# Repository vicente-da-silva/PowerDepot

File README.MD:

# Power Depot FJ Overland Build
## V1.0
The project started out with the goal of building a simple drawer system for my FJ. That simple goal turned into this Power Depot project! I may decide to split this project into 2 in the future as the Power Depot electronics evolve but for now the electrical and drawer system is presented as a single project.
Check out the detailed assembly document PowerDepotV1.pdf
It should be possible to easily create designs for other vehicles using the parts designed in this project.

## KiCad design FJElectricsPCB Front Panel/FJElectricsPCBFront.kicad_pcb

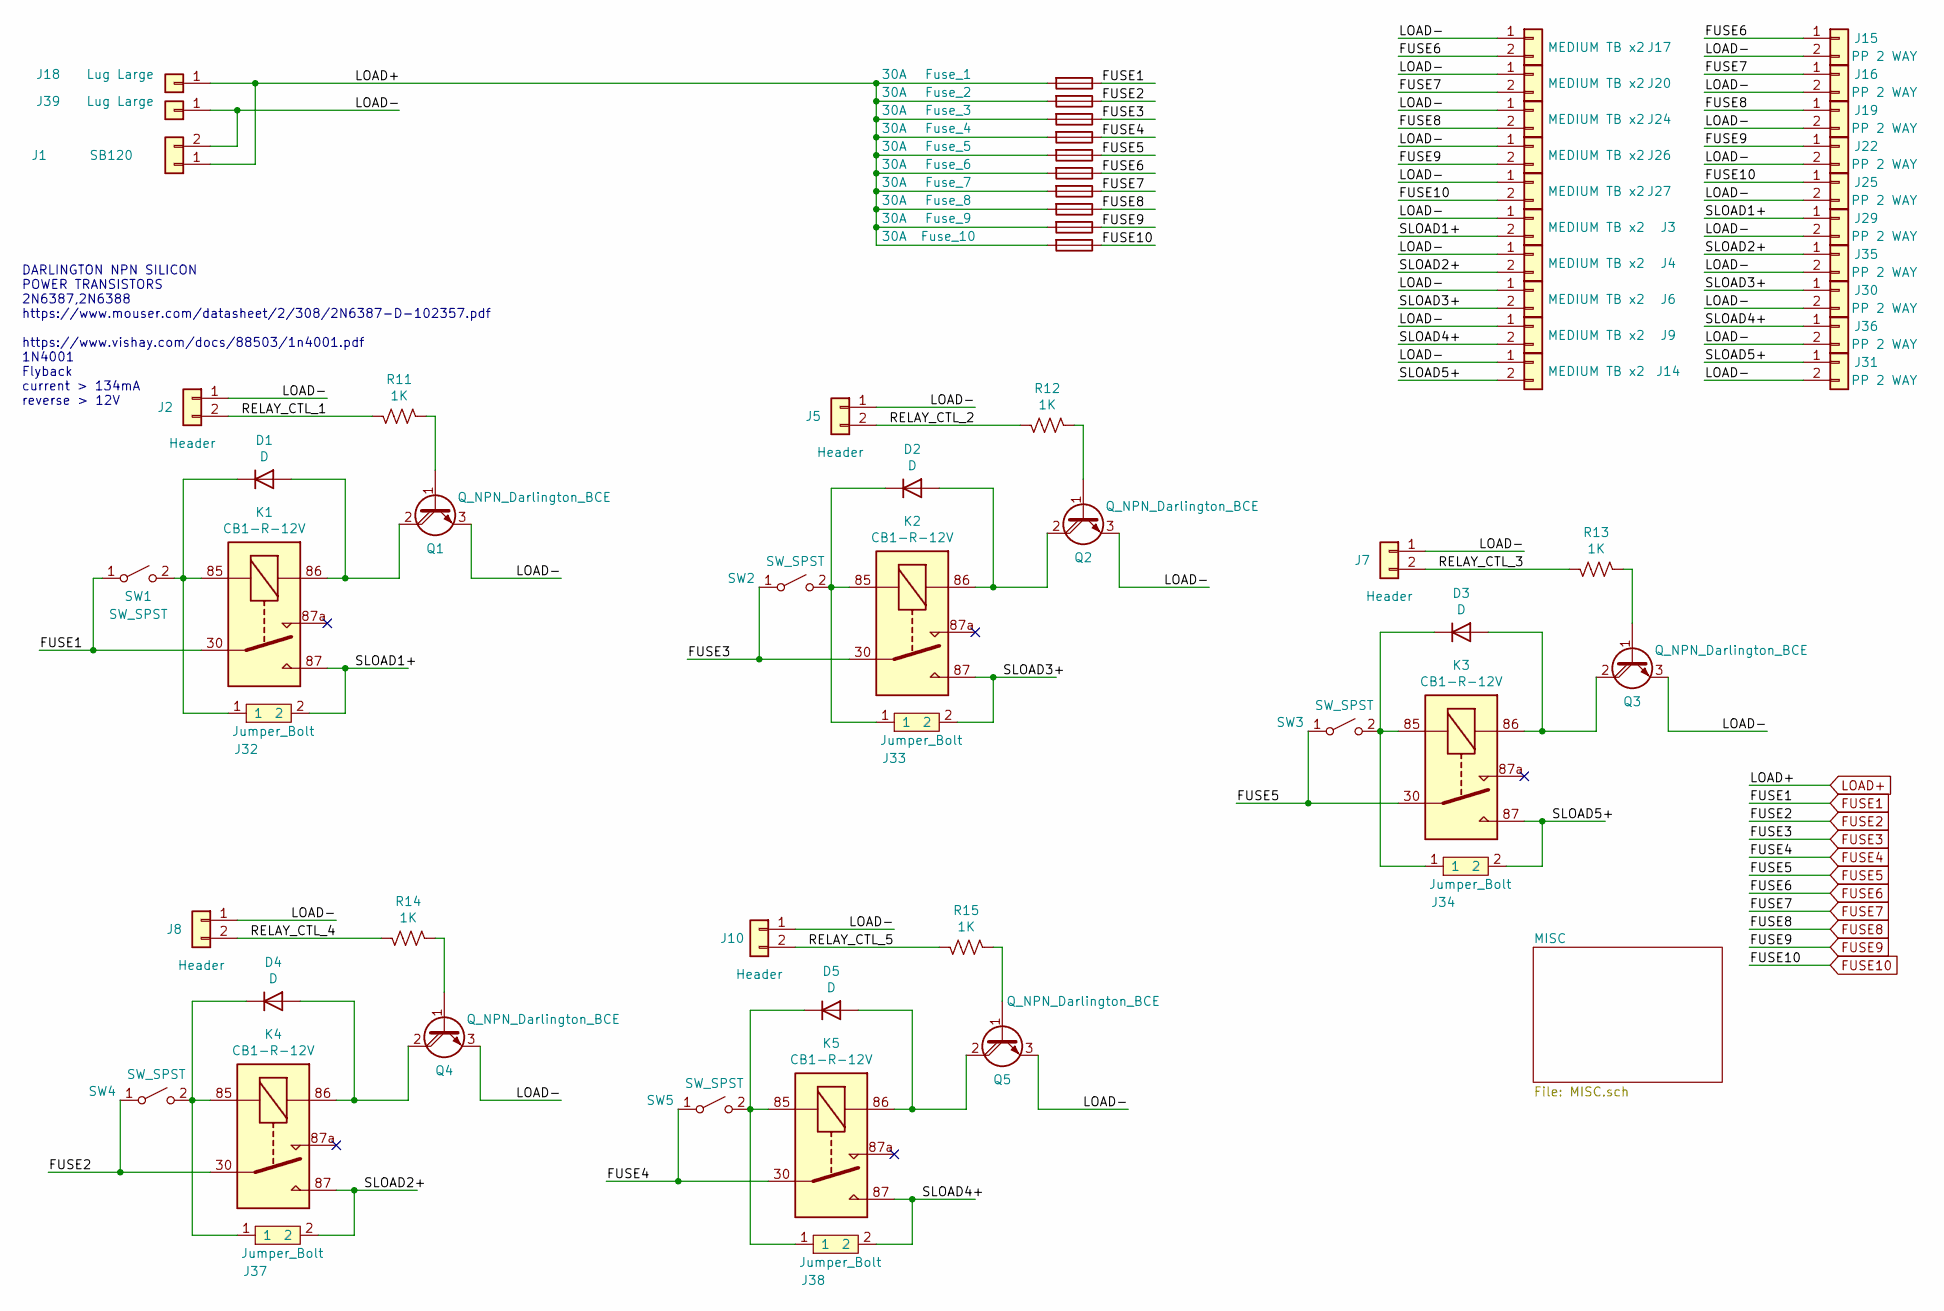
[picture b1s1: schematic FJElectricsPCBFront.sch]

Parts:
D1, D2, D3, D4, D5: D; D_DO-41_SOD81_P10.16mm_Horizontal
Fuse_1, Fuse_2, Fuse_3, Fuse_4, Fuse_5, Fuse_6, Fuse_7, Fuse_8, Fuse_9, Fuse_10: 30A; FuseHolder20x5Fuse
J1: SB120; SA120
J2, J5, J7, J8, J10: Header; TerminalBlock_Phoenix_MPT-0,5-2-2.54_1x02_P2.54mm_Horizontal
J3, J4, J6, J9, J14, J17, J20, J24, J26, J27: MEDIUM TB x2; TerminalBlock_7.62_2x1
J15, J16, J19, J22, J25, J29, J30, J31, J35, J36: PP 2 WAY; PowerPole_15_45
J18, J39: Lug Large; TerminalM20_x1
J32, J33, J34, J37, J38: Jumper_Bolt; ScrewM4Jumper
K1, K2, K3, K4, K5: CB1-R-12V; Relay_PCB_Socket_V23333
Q1, Q2, Q3, Q4, Q5: Q_NPN_Darlington_BCE; TO-220-3_Vertical
R11, R12, R13, R14, R15: 1K; R_Axial_DIN0207_L6.3mm_D2.5mm_P10.16mm_Horizontal
SW1, SW2, SW3, SW4, SW5: SW_SPST; SwitchMount

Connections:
/LOAD-: J1.2, J2.1, J3.1, J4.1, J5.1, J6.1, J7.1, J8.1, J9.1, J10.1, J14.1, J15.2, J16.2, J17.1, J19.2, J20.1, J22.2, J24.1, J25.2, J26.1, J27.1, J29.2, J30.2, J31.2, J35.2, J36.2, J39.1, Q1.3 (E), Q2.3 (E), Q3.3 (E), Q4.3 (E), Q5.3 (E)
/RELAY_CTL_1: J2.2, R11.1
/RELAY_CTL_2: J5.2, R12.1
/RELAY_CTL_3: J7.2, R13.1
/RELAY_CTL_4: J8.2, R14.1
/RELAY_CTL_5: J10.2, R15.1
/SLOAD1+: J3.2, J29.1, J32.2, K1.87
/SLOAD2+: J4.2, J35.1, J37.2, K4.87
/SLOAD3+: J6.2, J30.1, J33.2, K2.87
/SLOAD4+: J9.2, J36.1, J38.2, K5.87
/SLOAD5+: J14.2, J31.1, J34.2, K3.87
FUSE1: Fuse_1.1, K1.30, SW1.1 (A); also elsewhere on the board
FUSE2: Fuse_2.1, K4.30, SW4.1 (A); also elsewhere on the board
FUSE3: Fuse_3.1, K2.30, SW2.1 (A); also elsewhere on the board
FUSE4: Fuse_4.1, K5.30, SW5.1 (A); also elsewhere on the board
FUSE5: Fuse_5.1, K3.30, SW3.1 (A); also elsewhere on the board
FUSE6: Fuse_6.1, J15.1, J17.2; also elsewhere on the board
FUSE7: Fuse_7.1, J16.1, J20.2; also elsewhere on the board
FUSE8: Fuse_8.1, J19.1, J24.2; also elsewhere on the board
FUSE9: Fuse_9.1, J22.1, J26.2; also elsewhere on the board
FUSE10: Fuse_10.1, J25.1, J27.2; also elsewhere on the board
LOAD+: Fuse_1.2, Fuse_2.2, Fuse_3.2, Fuse_4.2, Fuse_5.2, Fuse_6.2, Fuse_7.2, Fuse_8.2, Fuse_9.2, Fuse_10.2, J1.1, J18.1; also elsewhere on the board
unnamed: D1.1 (K), J32.1, K1.85, SW1.2 (B)
unnamed: D1.2 (A), K1.86, Q1.2 (C)
unnamed: D2.1 (K), J33.1, K2.85, SW2.2 (B)
unnamed: D2.2 (A), K2.86, Q2.2 (C)
unnamed: D3.1 (K), J34.1, K3.85, SW3.2 (B)
unnamed: D3.2 (A), K3.86, Q3.2 (C)
unnamed: D4.1 (K), J37.1, K4.85, SW4.2 (B)
unnamed: D4.2 (A), K4.86, Q4.2 (C)
unnamed: D5.1 (K), J38.1, K5.85, SW5.2 (B)
unnamed: D5.2 (A), K5.86, Q5.2 (C)
unnamed: Q1.1 (B), R11.2
unnamed: Q2.1 (B), R12.2
unnamed: Q3.1 (B), R13.2
unnamed: Q4.1 (B), R14.2
unnamed: Q5.1 (B), R15.2

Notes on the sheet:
DARLINGTON NPN SILICON POWER TRANSISTORS 2N6387,2N6388 https://www.mouser.com/datasheet/2/308/2N6387-D-102357.pdf https://www.vishay.com/docs/88503/1n4001.pdf 1N4001 Flyback current > 134mA reverse > 12V

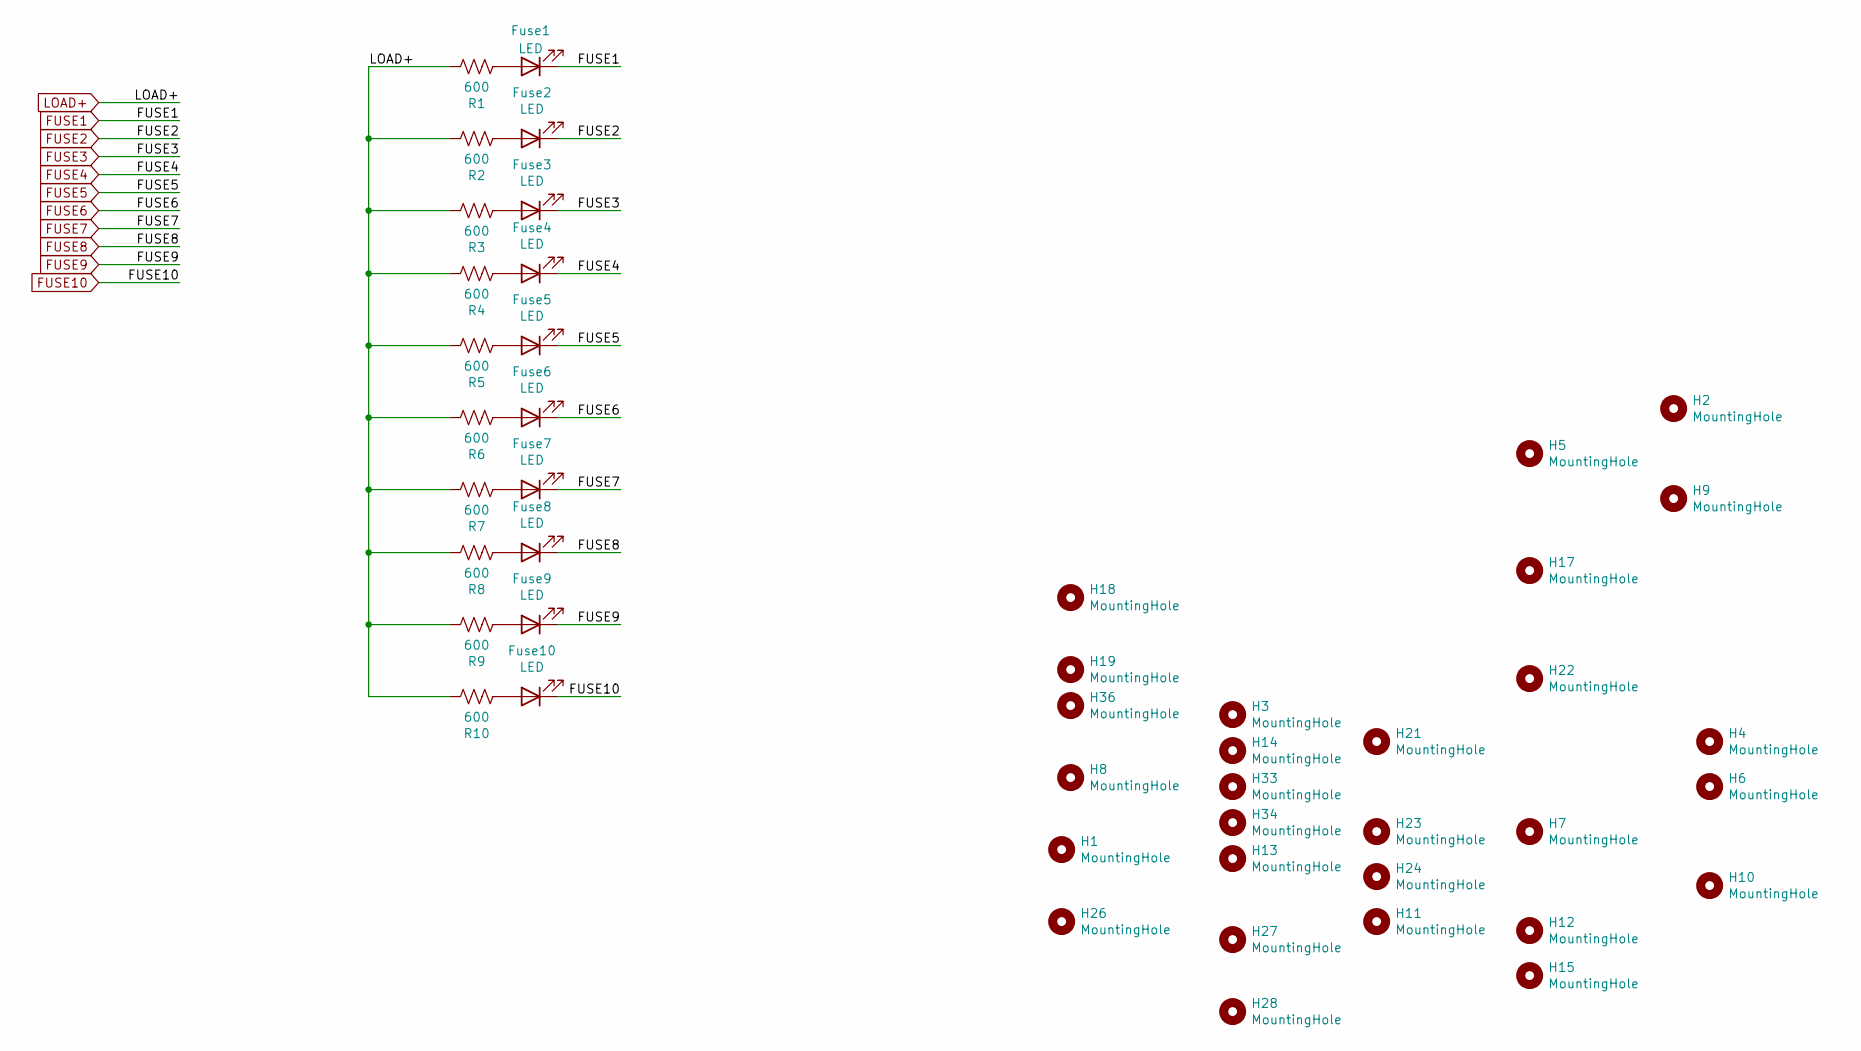
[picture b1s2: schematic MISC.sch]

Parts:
Fuse1, Fuse2, Fuse3, Fuse4, Fuse5, Fuse6, Fuse7, Fuse8, Fuse9, Fuse10: LED; LED_D5.0mm
H1, H2, H3, H4, H5, H6, H7, H8, H9, H10, H11, H12, H13, H14, H15, H17, H18, H19, H21, H22, H23, H24, H26, H27, H28, H33, H34, H36: MountingHole; NPTH_3mm_ID
R1, R2, R3, R4, R5, R6, R7, R8, R9, R10: 600; R_Axial_DIN0207_L6.3mm_D2.5mm_P10.16mm_Horizontal

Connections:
FUSE1: Fuse1.1 (K); also elsewhere on the board
FUSE2: Fuse2.1 (K); also elsewhere on the board
FUSE3: Fuse3.1 (K); also elsewhere on the board
FUSE4: Fuse4.1 (K); also elsewhere on the board
FUSE5: Fuse5.1 (K); also elsewhere on the board
FUSE6: Fuse6.1 (K); also elsewhere on the board
FUSE7: Fuse7.1 (K); also elsewhere on the board
FUSE8: Fuse8.1 (K); also elsewhere on the board
FUSE9: Fuse9.1 (K); also elsewhere on the board
FUSE10: Fuse10.1 (K); also elsewhere on the board
LOAD+: R1.1, R2.1, R3.1, R4.1, R5.1, R6.1, R7.1, R8.1, R9.1, R10.1; also elsewhere on the board
unnamed: Fuse1.2 (A), R1.2
unnamed: Fuse2.2 (A), R2.2
unnamed: Fuse3.2 (A), R3.2
unnamed: Fuse4.2 (A), R4.2
unnamed: Fuse5.2 (A), R5.2
unnamed: Fuse6.2 (A), R6.2
unnamed: Fuse7.2 (A), R7.2
unnamed: Fuse8.2 (A), R8.2
unnamed: Fuse9.2 (A), R9.2
unnamed: Fuse10.2 (A), R10.2

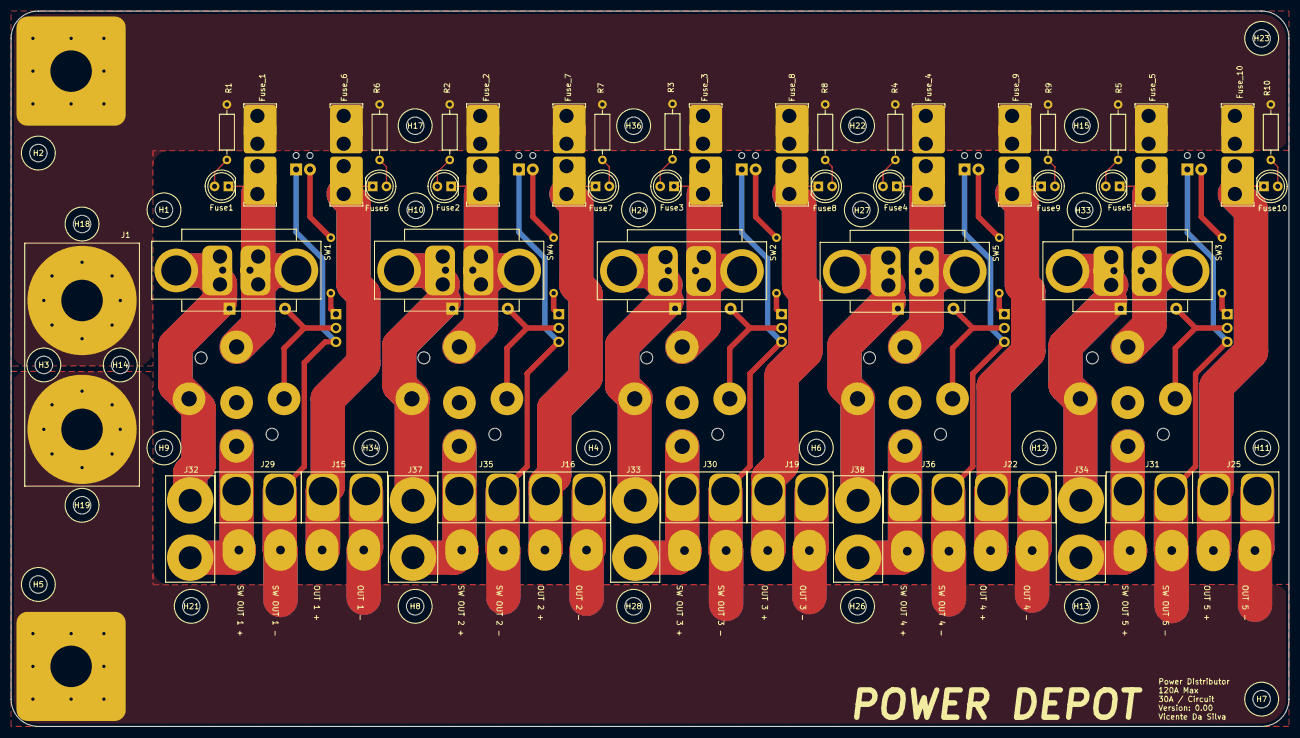
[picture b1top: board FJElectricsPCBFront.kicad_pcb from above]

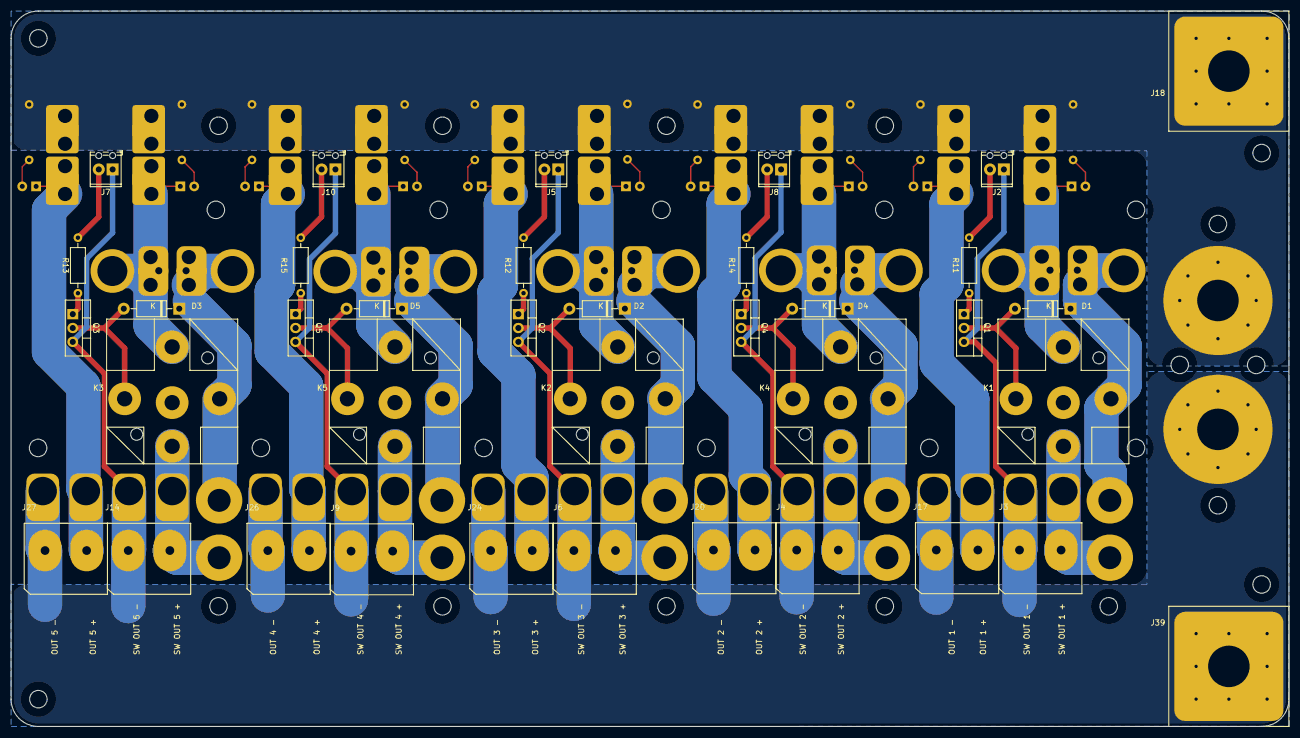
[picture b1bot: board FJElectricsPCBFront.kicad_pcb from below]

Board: 2 copper layers, 234.0 x 131.0 mm, 116 parts (37 on the bottom side), 47 nets.

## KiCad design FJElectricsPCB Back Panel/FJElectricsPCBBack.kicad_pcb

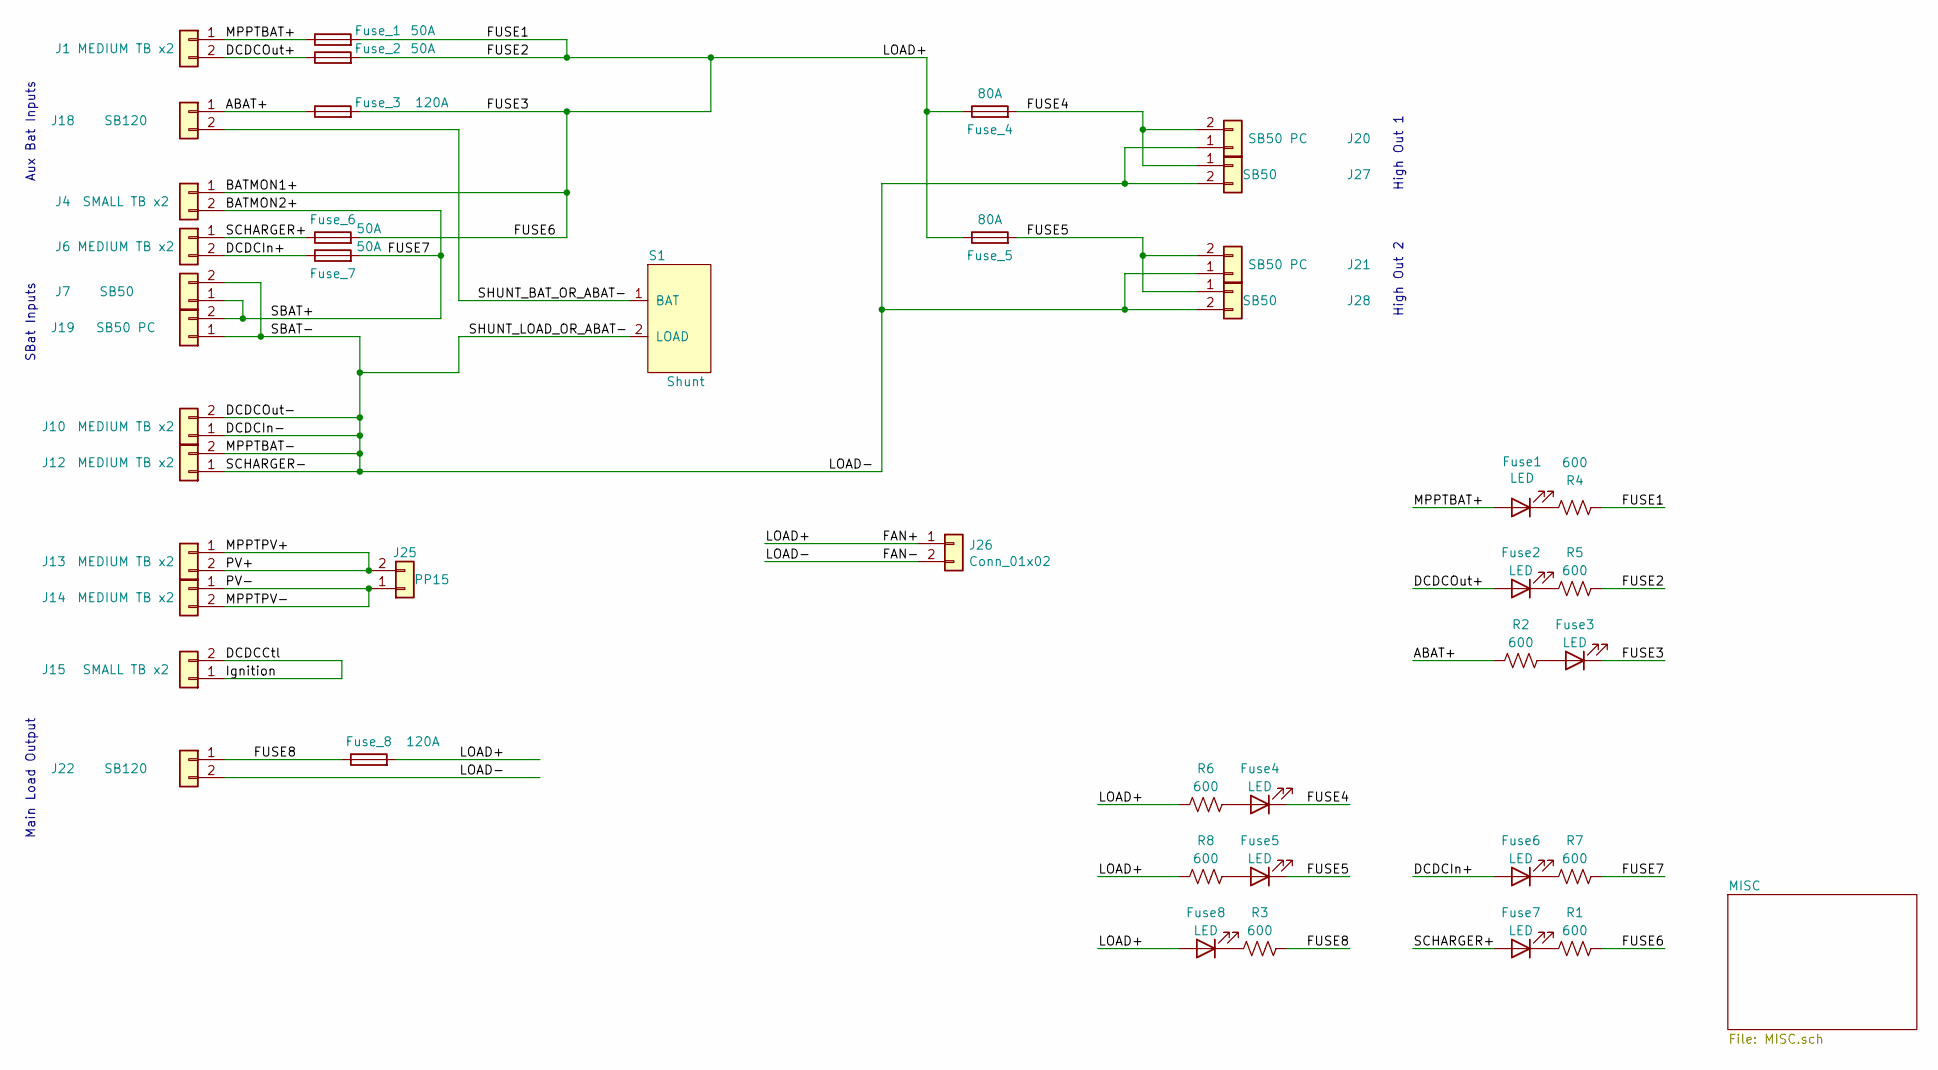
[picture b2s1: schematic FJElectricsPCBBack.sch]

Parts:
Fuse1, Fuse2, Fuse3, Fuse4, Fuse5, Fuse6, Fuse7, Fuse8: LED; LED_D5.0mm
Fuse_1, Fuse_2, Fuse_6, Fuse_7: 50A; FuseHolderMaxi
Fuse_3, Fuse_8: 120A; FuseHolderMaxiWithMega
Fuse_4, Fuse_5: 80A; FuseHolderMaxi
J1, J6, J10, J12, J13, J14: MEDIUM TB x2; TerminalBlock_7.62_2x1
J4, J15: SMALL TB x2; TerminalBlock_5_2x1
J7, J27, J28: SB50; SA50_2
J18, J22: SB120; SA120
J19, J20, J21: SB50 PC; SA50
J25: PP15; PowerPole_15_45
J26: Conn_01x02; PinHeader_1x02_P2.54mm_Vertical
R1, R2, R3, R4, R5, R6, R7, R8: 600; R_Axial_DIN0207_L6.3mm_D2.5mm_P10.16mm_Horizontal
S1: Shunt

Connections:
/ABAT+: Fuse_3.1, J18.1, R2.1
/BATMON1+: Fuse3.1 (K), Fuse8.2 (A), Fuse_1.2, Fuse_2.2, Fuse_3.2, Fuse_4.1, Fuse_5.1, Fuse_6.2, Fuse_8.2, J4.1, J26.1, R1.2, R4.2, R5.2, R6.1, R8.1
/BATMON2+: Fuse_7.2, J4.2, J7.1, J19.2, R7.2
/DCDCCtl: J15.1, J15.2
/DCDCIn+: Fuse6.2 (A), Fuse_7.1, J6.2
/DCDCIn-: J7.2, J10.1, J10.2, J12.1, J12.2, J19.1, J20.1, J21.1, J22.2, J26.2, J27.2, J28.2, S1.2 (LOAD)
/DCDCOut+: Fuse2.2 (A), Fuse_2.1, J1.2
/FUSE4: Fuse4.1 (K), Fuse_4.2, J20.2, J27.1
/FUSE5: Fuse5.1 (K), Fuse_5.2, J21.2, J28.1
/FUSE8: Fuse_8.1, J22.1, R3.2
/MPPTBAT+: Fuse1.2 (A), Fuse_1.1, J1.1
/MPPTPV+: J13.1, J13.2, J25.2
/MPPTPV-: J14.1, J14.2, J25.1
/SCHARGER+: Fuse7.2 (A), Fuse_6.1, J6.1
/SHUNT_BAT_OR_ABAT-: J18.2, S1.1 (BAT)
unnamed: Fuse1.1 (K), R4.1
unnamed: Fuse2.1 (K), R5.1
unnamed: Fuse3.2 (A), R2.2
unnamed: Fuse4.2 (A), R6.2
unnamed: Fuse5.2 (A), R8.2
unnamed: Fuse6.1 (K), R7.1
unnamed: Fuse7.1 (K), R1.1
unnamed: Fuse8.1 (K), R3.1

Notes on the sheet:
SBat Inputs
Aux Bat Inputs
Main Load Output
High Out 1
High Out 2

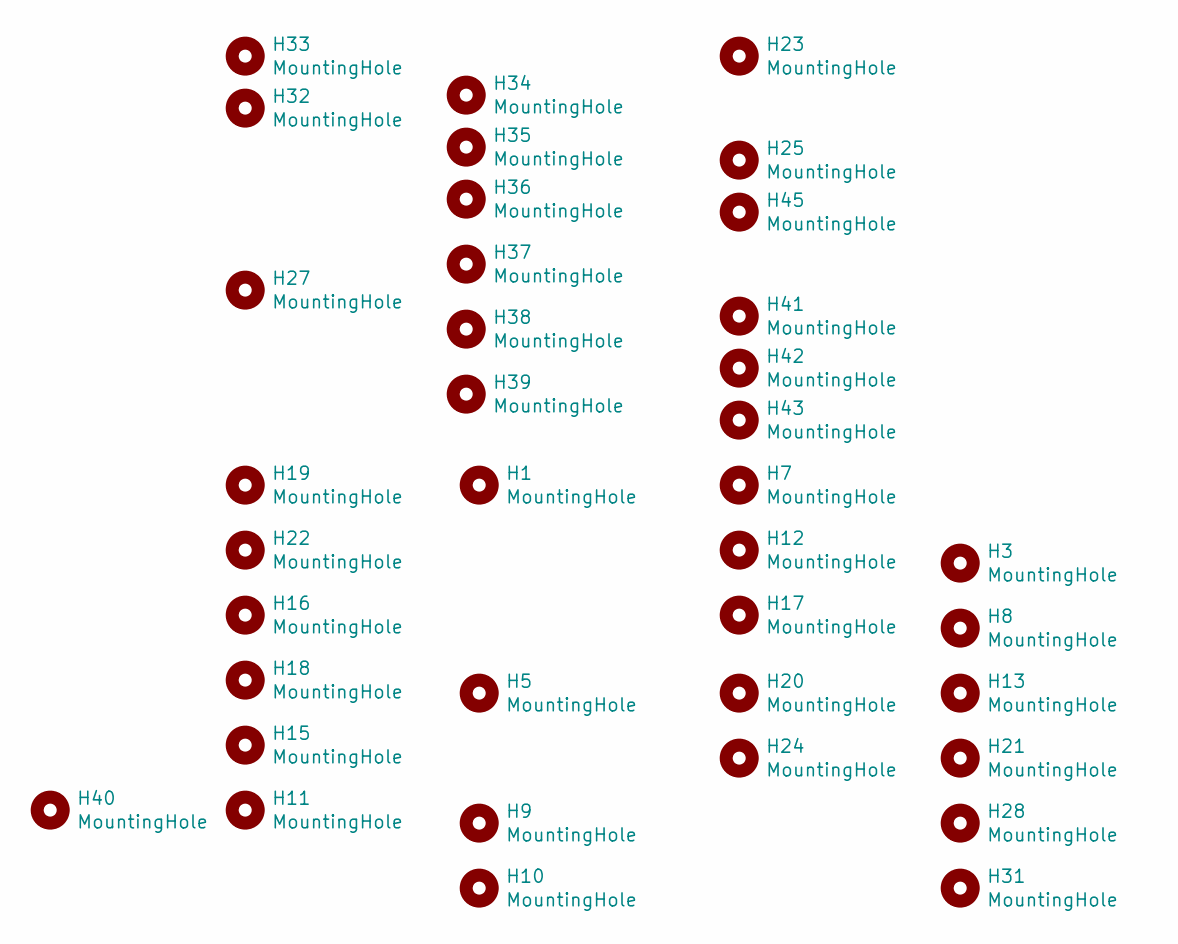
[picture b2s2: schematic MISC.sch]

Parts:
H1, H3, H5, H7, H8, H9, H10, H11, H12, H13, H15, H16, H17, H18, H19, H20, H21, H22, H23, H24, H25, H27, H28, H31, H32, H33, H34, H35, H36, H37, H38, H39, H40, H41, H42, H43, H45: MountingHole; NPTH_3mm_ID

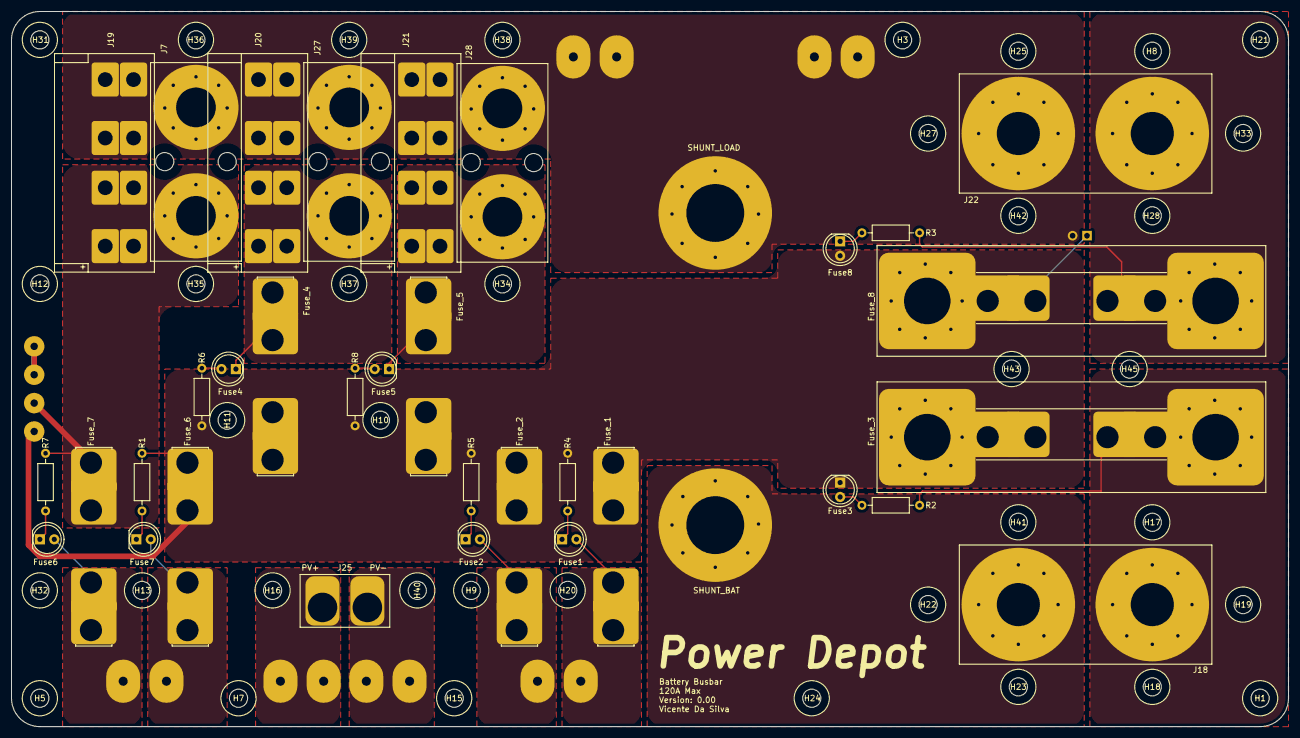
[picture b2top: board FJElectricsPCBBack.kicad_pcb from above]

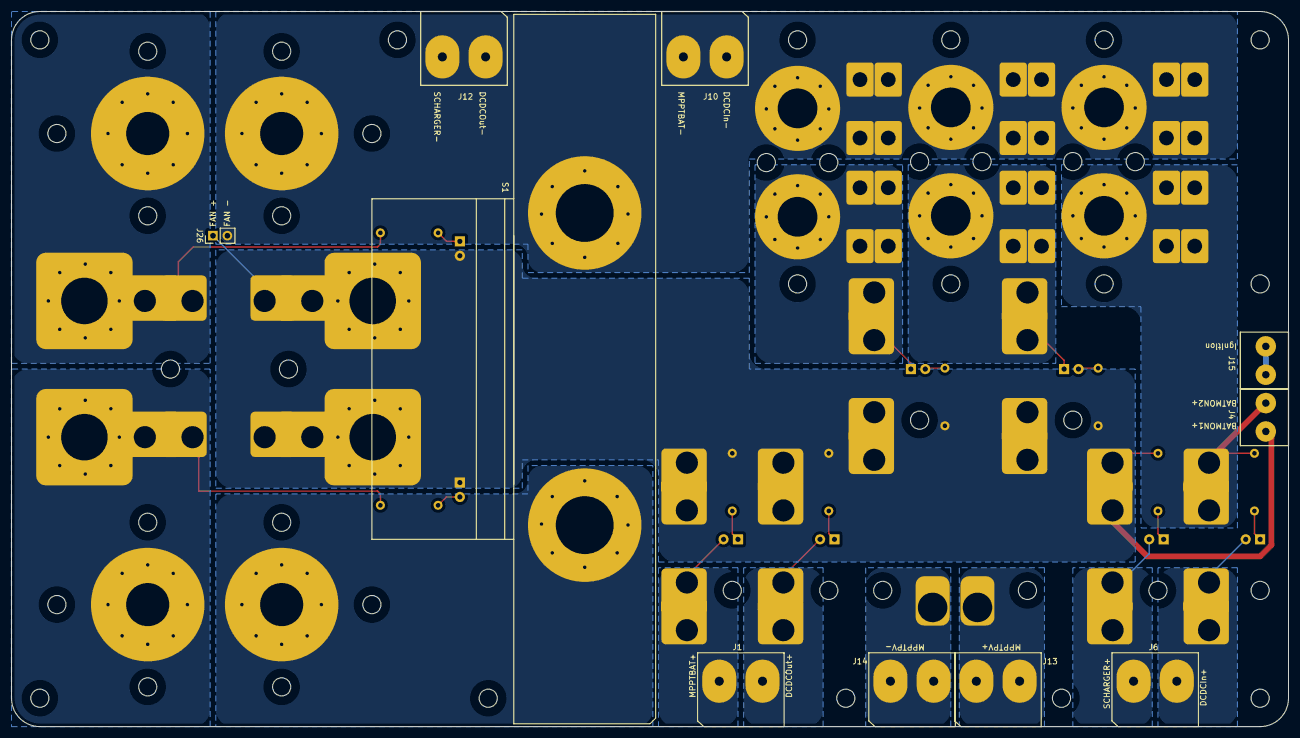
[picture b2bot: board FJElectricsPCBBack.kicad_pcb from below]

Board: 2 copper layers, 225.0 x 126.0 mm, 80 parts (10 on the bottom side), 23 nets.

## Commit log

2022-01-10 add images
2022-01-10 added image
2022-01-16 Added images to Readme
